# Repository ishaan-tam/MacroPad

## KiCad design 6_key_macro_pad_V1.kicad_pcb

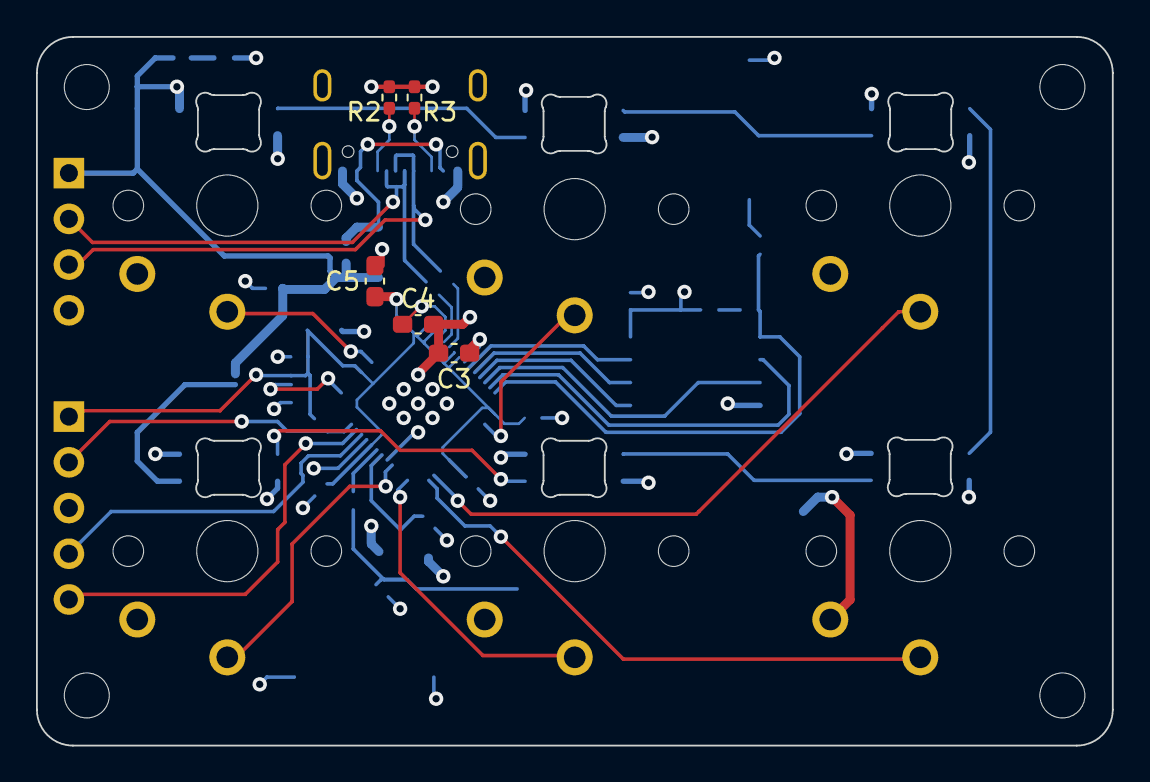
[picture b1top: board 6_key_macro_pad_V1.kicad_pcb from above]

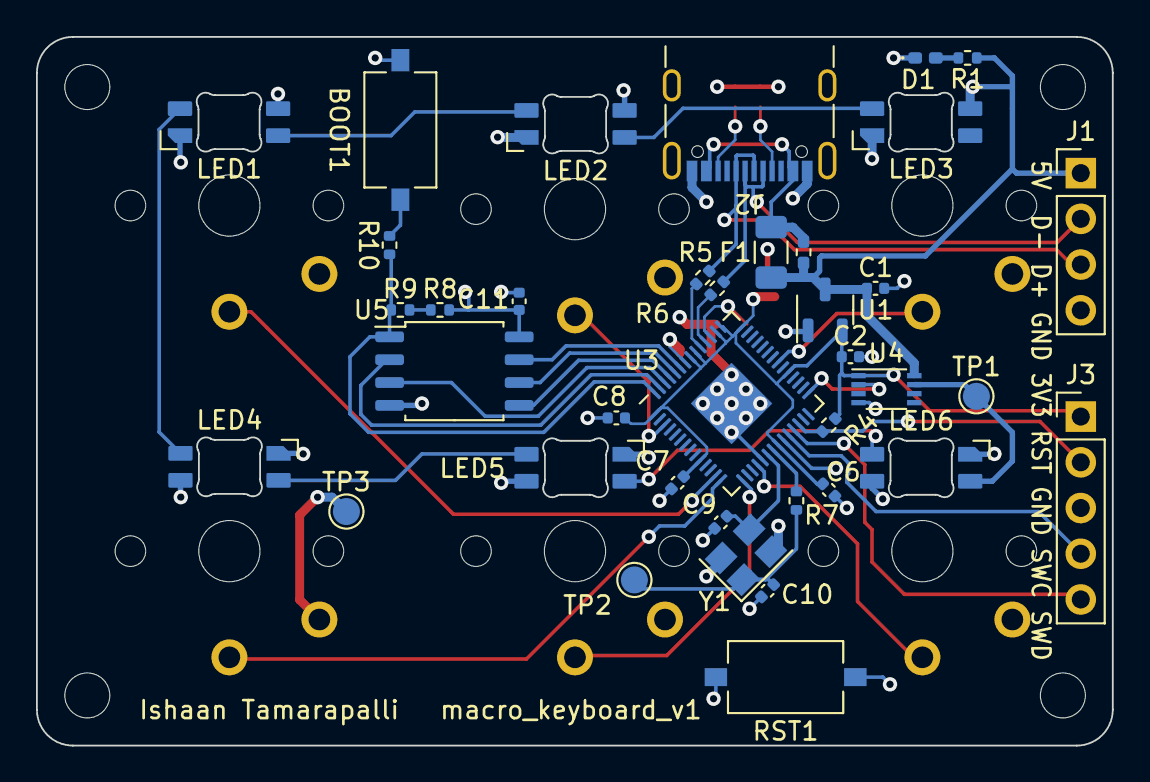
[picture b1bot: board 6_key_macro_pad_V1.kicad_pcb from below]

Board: 4 copper layers, 59.8 x 39.4 mm, 53 parts (42 on the bottom side), 39 nets.

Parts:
BOOT1: SW_Push; SW_Tactile_SPST_NO_Straight_CK_PTS636Sx25SMTRLFS
C1, C2: 1u; C_0402_1005Metric
C3: 1u; C_0603_1608Metric_Pad1.08x0.95mm_HandSolder
C4: 100n; C_0603_1608Metric_Pad1.08x0.95mm_HandSolder
C5: 10u; C_0603_1608Metric_Pad1.08x0.95mm_HandSolder
C6, C7, C8, C11: 100n; C_0402_1005Metric
C9, C10: 22p; C_0402_1005Metric
CH7, CH8, CH9, CH10, CH11, CH12: choc_SW_solder; SW_choc_v1_1u
D1: RED; LED_0402_1005Metric_Pad0.77x0.64mm_HandSolder
F1: Fuse_Small; Fuse_1206_3216Metric
H1, H2, H3, H4: MountingHole; MountingHole_2.5mm
J1: Conn_01x04; PinHeader_1x04_P2.54mm_Vertical
J2: USB_C_Receptacle_USB2.0; USB_C_Receptacle_GCT_USB4105-xx-A_16P_TopMnt_Horizontal
J3: Conn_01x05; PinHeader_1x05_P2.54mm_Vertical
LED1, LED2, LED3, LED4, LED5, LED6: choc_SK6812MINI-E; LED_choc_6028R
R1: 1k5; R_0402_1005Metric
R2, R3: 5k1; R_0402_1005Metric_Pad0.72x0.64mm_HandSolder
R4, R8, R9: 5k1; R_0402_1005Metric
R5, R6: 27; R_0402_1005Metric
R7, R10: 1k; R_0402_1005Metric
R11: 0; R_0402_1005Metric_Pad0.72x0.64mm_HandSolder
RST1: SW_Push; SW_Tactile_SPST_NO_Straight_CK_PTS636Sx25SMTRLFS
TP1, TP2, TP3: TestPoint; TestPoint_Pad_D1.5mm
U1: XC6206PxxxMR; SOT-23-3
U3: RP2040; QFN-56-1EP_7x7mm_P0.4mm_EP3.2x3.2mm
U4: 74LVC2T45DC; VSSOP-8_2.3x2mm_P0.5mm
U5: W25Q128JVS; SOIC-8_5.23x5.23mm_P1.27mm
Y1: 12MHz; Crystal_SMD_3225-4Pin_3.2x2.5mm

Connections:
+1V1: C3.1, C4.1, U3.23 (DVDD), U3.45 (VREG_VOUT), U3.50 (DVDD)
+3V3: C2.1, C5.1, C6.1, C7.1, C8.1, C11.1, CH7.1, CH8.1, CH9.1, CH10.1, CH11.1, CH12.1, J3.1, R4.2, R8.2, TP3.1, U1.2 (VO), U3.1 (IOVDD), U3.10 (IOVDD), U3.22 (IOVDD), U3.33 (IOVDD), U3.42 (IOVDD), U3.43 (ADC_AVDD), U3.44 (VREG_IN), U3.48 (USB_VDD), U3.49 (IOVDD), U4.1 (VCCA), U5.8 (VCC)
+5V: C1.1, F1.2, J1.1, LED1.1 (VDD), LED2.1 (VDD), LED3.1 (VDD), LED4.1 (VDD), LED5.1 (VDD), LED6.1 (VDD), R1.1, R11.2, U1.3 (VI), U4.8 (VCCB)
/GPIO1: CH8.2, U3.3 (GPIO1)
/GPIO10: CH9.2, U3.13 (GPIO10)
/GPIO11: CH12.2, U3.14 (GPIO11)
/GPIO12: CH11.2, U3.15 (GPIO12)
/GPIO15: CH10.2, U3.18 (GPIO15)
/GPIO23: CH7.2, U3.35 (GPIO23)
/LED_CTRL_3V3: U3.29 (GPIO18), U4.2 (1A)
/LED_CTRL_5V: LED6.3 (DIN), TP1.1, U4.7 (1B)
/Q_CLK: U3.52 (QSPI_SCLK), U5.6 (CLK)
/Q_IO0: U3.53 (QSPI_SD0), U5.5 (DI(IO0))
/Q_IO1: U3.55 (QSPI_SD1), U5.2 (DO(IO1))
/Q_IO2: U3.54 (QSPI_SD2), U5.3 (IO2)
/Q_IO3: U3.51 (QSPI_SD3), U5.7 (IO3)
/Q_SEL: R9.1, R10.1, U3.56 (QSPI_SS), U5.1 (~CS)
/RESET: J3.2, R4.1, RST1.2, U3.26 (RUN)
/SWC: J3.4, U3.24 (SWCLK)
/SWD: J3.5, U3.25 (SWD)
/USB_D+: J1.3, J2.A6 (D+), J2.B6 (D+), R5.2
/USB_D-: J1.2, J2.A7 (D-), J2.B7 (D-), R6.2
/XIN: C9.2, U3.20 (XIN), Y1.3
/XOUT: R7.1, U3.21 (XOUT)
GND: BOOT1.1, C1.2, C2.2, C3.2, C4.2, C5.2, C6.2, C7.2, C8.2, C9.1, C10.2, C11.2, D1.1 (K), J1.4, J2.A1 (GND), J2.A12 (GND), J2.B1 (GND), J2.B12 (GND), J3.3, LED1.4 (VSS), LED2.4 (VSS), LED3.4 (VSS), LED4.4 (VSS), LED5.4 (VSS), LED6.4 (VSS), R2.2, R3.2, RST1.1, U1.1 (GND), U3.19 (TESTEN), U3.57 (GND), U4.4 (GND), U5.4 (GND), Y1.2, Y1.4
unnamed: BOOT1.2, R10.2
unnamed: C10.1, R7.2, TP2.1, Y1.1
unnamed: D1.2 (A), R1.2
unnamed: J2.A5 (CC1), R2.1
unnamed: J2.B5 (CC2), R3.1
unnamed: LED1.3 (DIN), LED4.2 (DOUT)
unnamed: LED1.2 (DOUT), LED2.3 (DIN)
unnamed: LED2.2 (DOUT), LED3.3 (DIN)
unnamed: LED4.3 (DIN), LED5.2 (DOUT)
unnamed: LED5.3 (DIN), LED6.2 (DOUT)
unnamed: R8.1, R9.2
unnamed: R6.1, U3.46 (USB_DM)
unnamed: R5.1, U3.47 (USB_DP)
VBUS: F1.1, J2.A4 (VBUS), J2.A9 (VBUS), J2.B4 (VBUS), J2.B9 (VBUS), R11.1
